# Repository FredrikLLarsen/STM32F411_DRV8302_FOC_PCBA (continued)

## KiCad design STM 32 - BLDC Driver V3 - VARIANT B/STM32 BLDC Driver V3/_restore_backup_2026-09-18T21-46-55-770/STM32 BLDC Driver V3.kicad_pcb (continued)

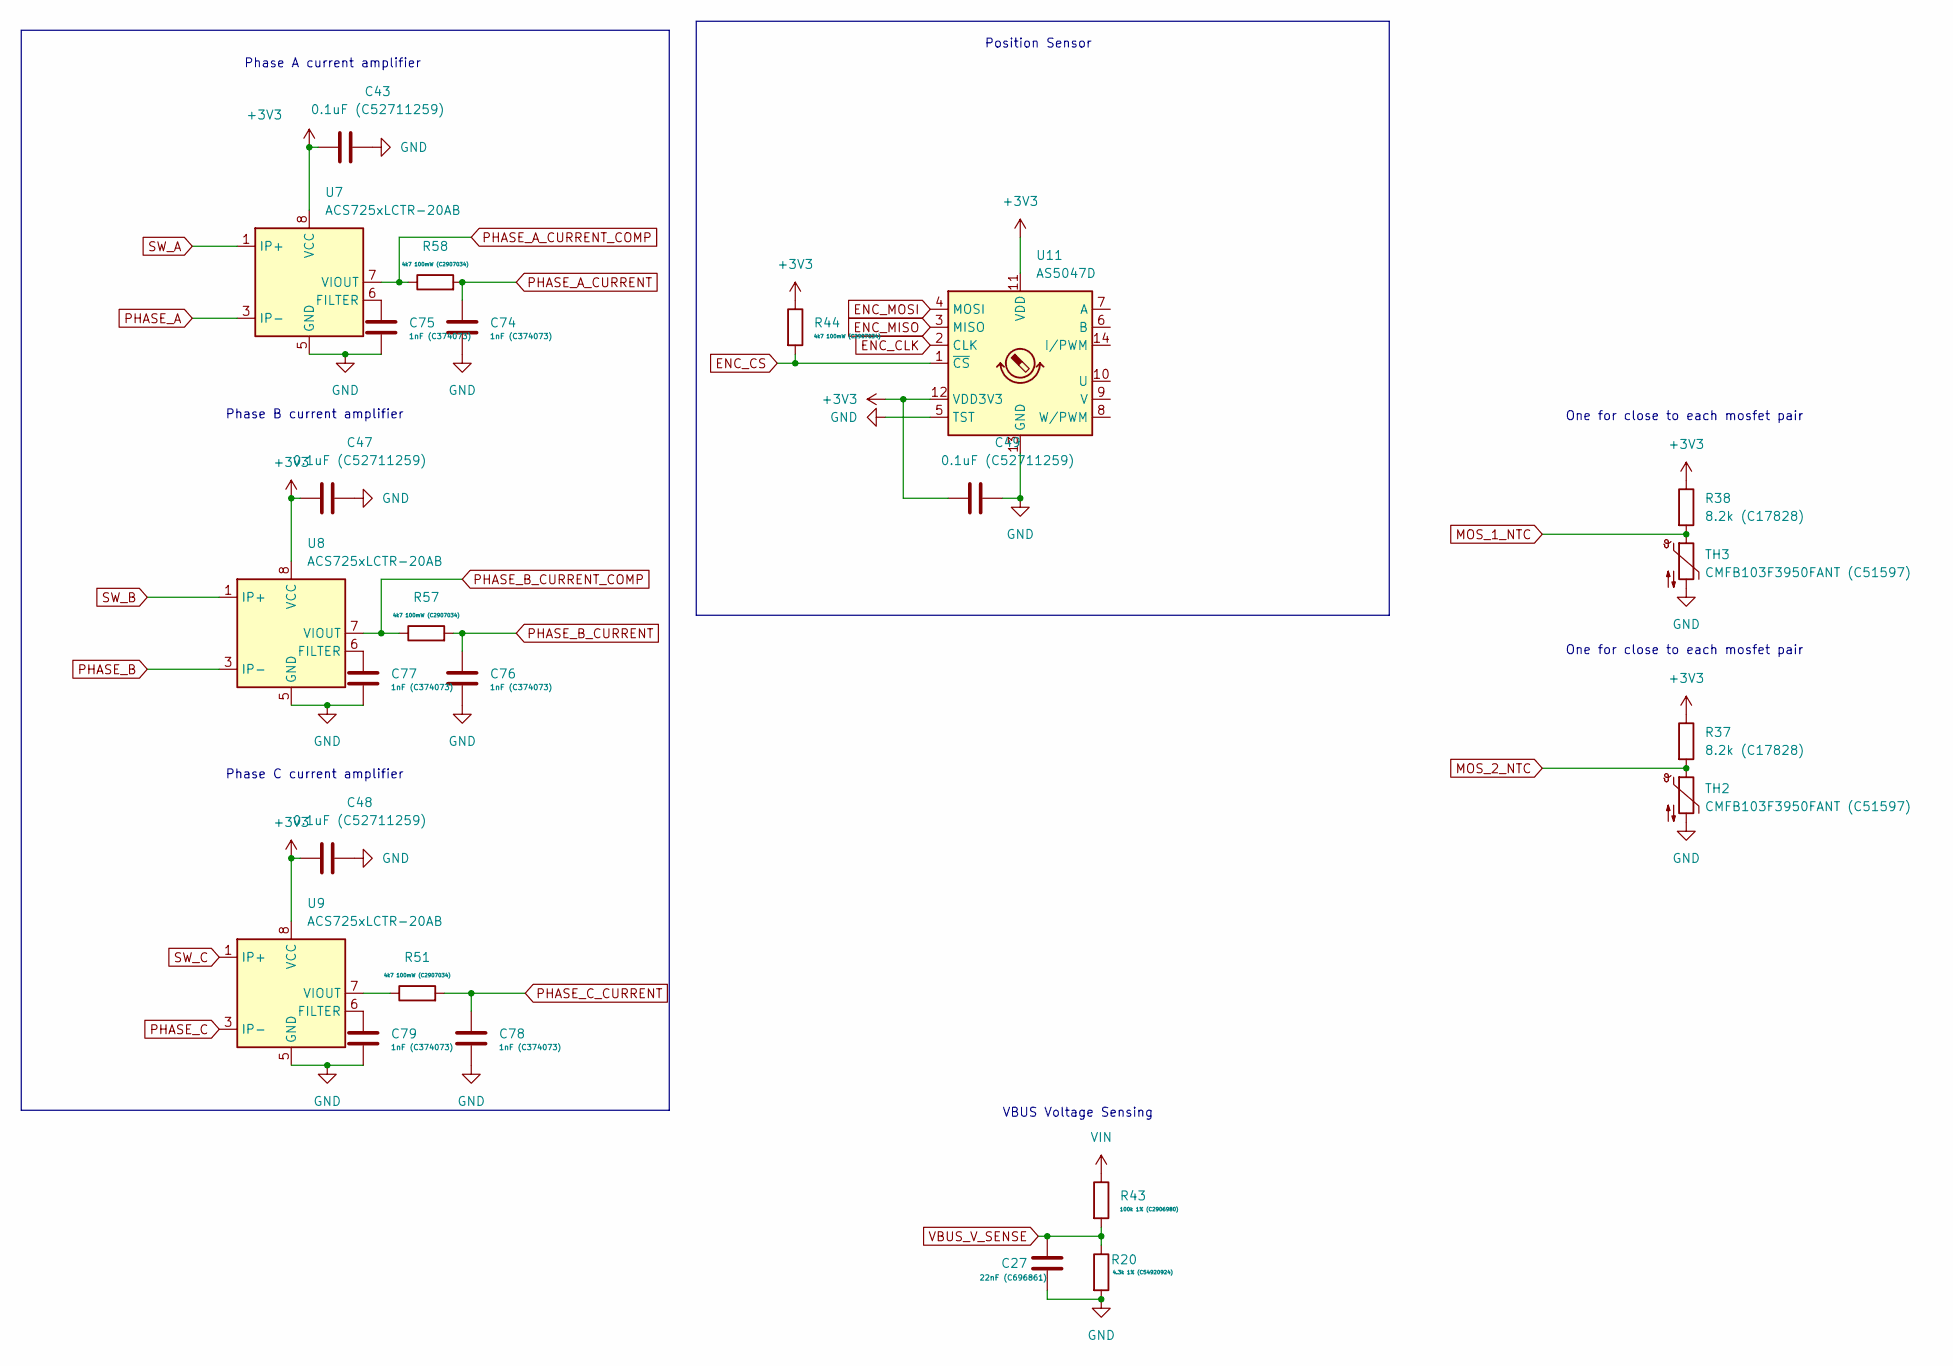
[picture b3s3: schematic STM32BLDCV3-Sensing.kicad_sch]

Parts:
C27: 22nF (C696861); C_0603_1608Metric_Pad1.08x0.95mm_HandSolder
C43, C47, C48, C49: 0.1uF (C52711259); C_0603_1608Metric_Pad1.08x0.95mm_HandSolder
C74, C75, C76, C77, C78, C79: 1nF (C374073); C_0603_1608Metric_Pad1.08x0.95mm_HandSolder
R20: 4.3k 1% (C54920924); R_0603_1608Metric_Pad0.98x0.95mm_HandSolder
R37, R38: 8.2k (C17828); R_0805_2012Metric_Pad1.20x1.40mm_HandSolder
R43: 100k 1% (C2906980); R_0603_1608Metric_Pad0.98x0.95mm_HandSolder
R44, R51, R57, R58: 4k7 100mW (C2907034); R_0603_1608Metric_Pad0.98x0.95mm_HandSolder
TH2, TH3: CMFB103F3950FANT (C51597); R_0805_2012Metric_Pad1.20x1.40mm_HandSolder
U7, U8, U9: ACS725xLCTR-20AB; SOIC-8_3.9x4.9mm_P1.27mm
U11: AS5047D; TSSOP-14_4.4x5mm_P0.65mm

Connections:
+3V3: C43.1, C47.1, C48.1, C49.1, R37.1, R38.1, R44.1, U7.8 (VCC), U8.8 (VCC), U9.8 (VCC), U11.11 (VDD), U11.12 (VDD3V3); also elsewhere on the board
ENC_CLK: U11.2 (CLK); also elsewhere on the board
ENC_CS: R44.2, U11.1 (~CS); also elsewhere on the board
ENC_MISO: U11.3 (MISO); also elsewhere on the board
ENC_MOSI: U11.4 (MOSI); also elsewhere on the board
GND: C27.2, C43.2, C47.2, C48.2, C49.2, C74.2, C75.2, C76.2, C77.2, C78.2, C79.2, R20.2, TH2.2, TH3.2, U7.5 (GND), U8.5 (GND), U9.5 (GND), U11.5 (TST), U11.13 (GND); also elsewhere on the board
MOS_1_NTC: R38.2, TH3.1; also elsewhere on the board
MOS_2_NTC: R37.2, TH2.1; also elsewhere on the board
unnamed: C75.1, U7.6 (FILTER)
unnamed: C77.1, U8.6 (FILTER)
unnamed: C79.1, U9.6 (FILTER)
unnamed: R51.1, U9.7 (VIOUT)
PHASE_A: U7.3 (IP-), U7.4 (IP-); also elsewhere on the board
PHASE_A_CURRENT: C74.1, R58.2; also elsewhere on the board
PHASE_A_CURRENT_COMP: R58.1, U7.7 (VIOUT); also elsewhere on the board
PHASE_B: U8.3 (IP-), U8.4 (IP-); also elsewhere on the board
PHASE_B_CURRENT: C76.1, R57.2; also elsewhere on the board
PHASE_B_CURRENT_COMP: R57.1, U8.7 (VIOUT); also elsewhere on the board
PHASE_C: U9.3 (IP-), U9.4 (IP-); also elsewhere on the board
PHASE_C_CURRENT: C78.1, R51.2; also elsewhere on the board
SW_A: U7.1 (IP+), U7.2 (IP+); also elsewhere on the board
SW_B: U8.1 (IP+), U8.2 (IP+); also elsewhere on the board
SW_C: U9.1 (IP+), U9.2 (IP+); also elsewhere on the board
VBUS_V_SENSE: C27.1, R20.1, R43.2; also elsewhere on the board
VIN: R43.1; also elsewhere on the board

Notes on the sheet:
Position Sensor
Phase A current amplifier
Phase B current amplifier
One for close to each mosfet pair
Phase C current amplifier
VBUS Voltage Sensing

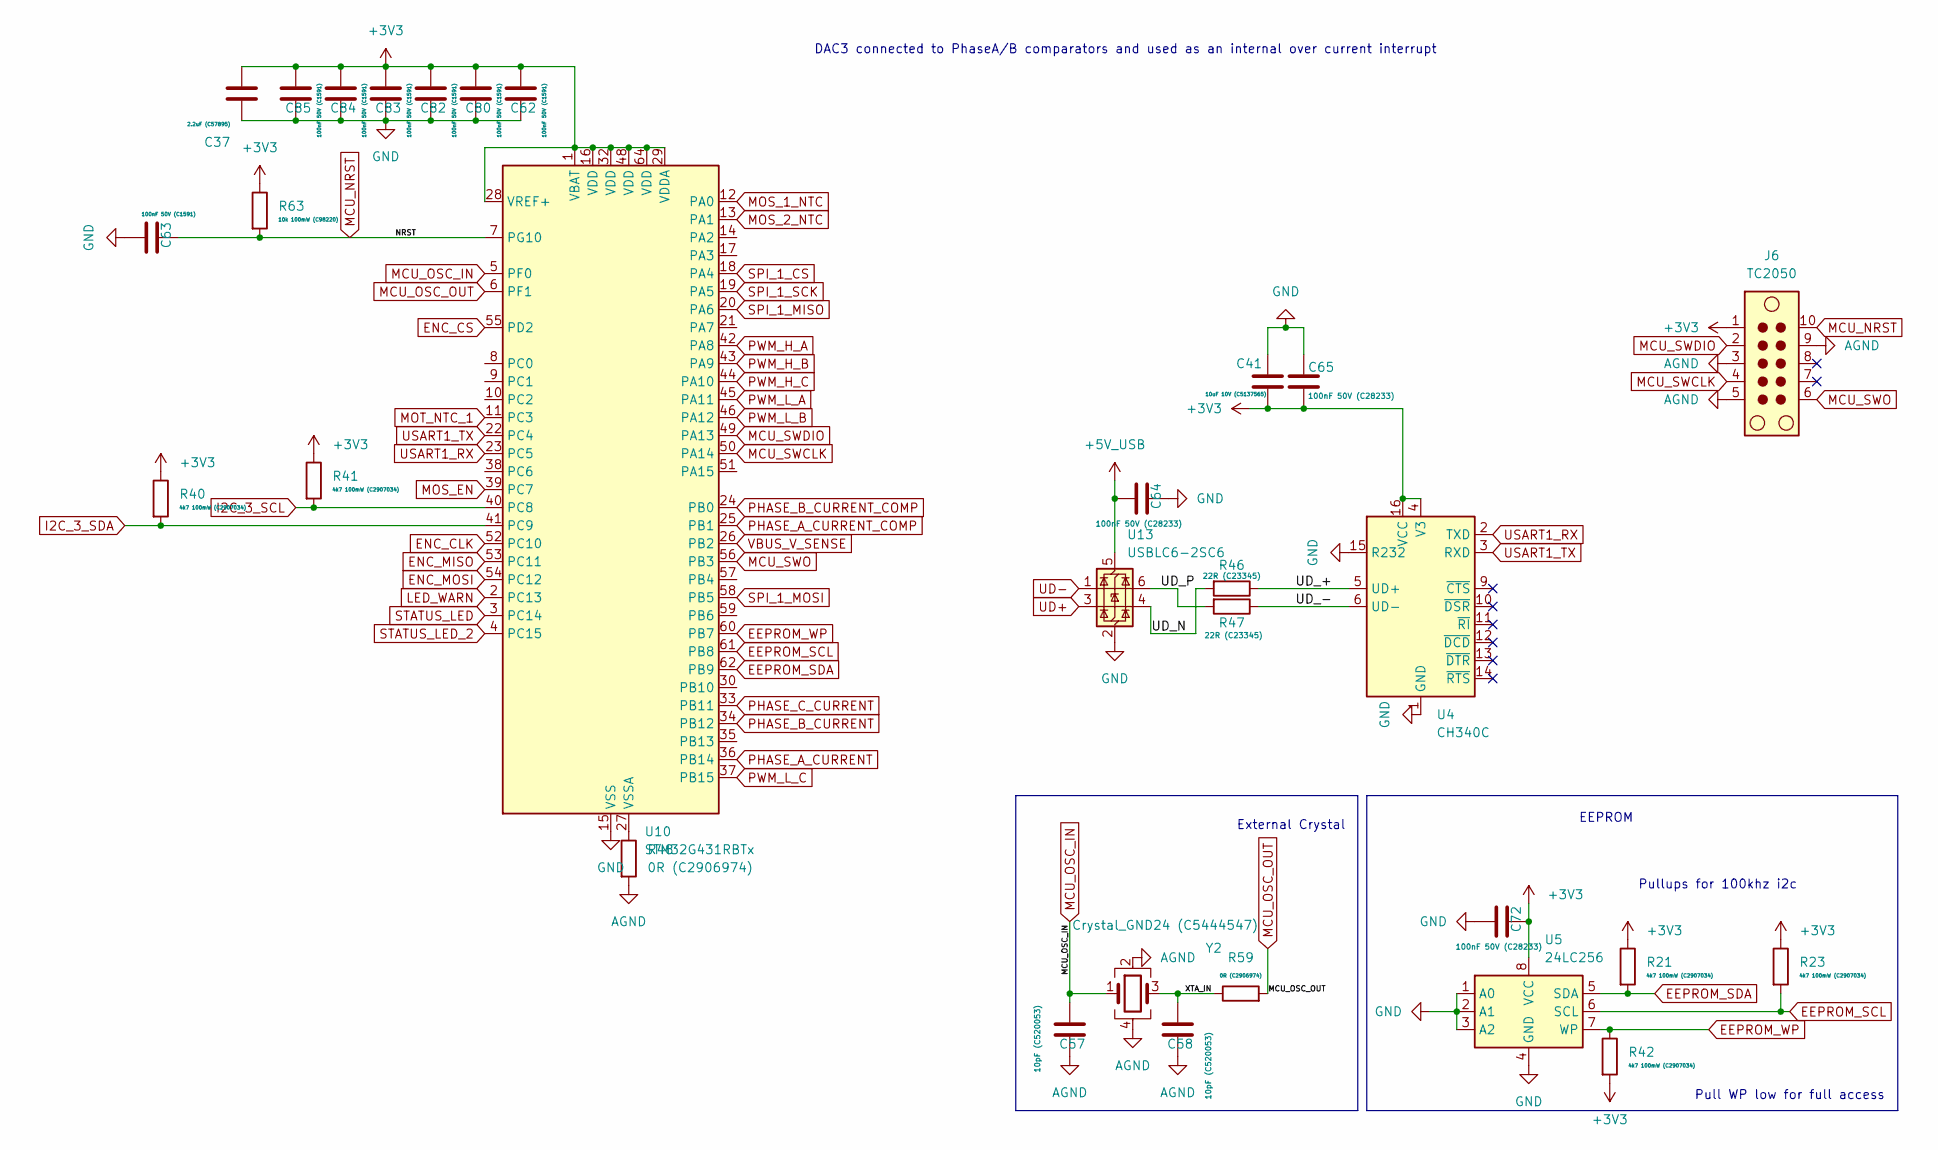
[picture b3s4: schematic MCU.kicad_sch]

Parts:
C37: 2.2uF (C57895); C_0603_1608Metric_Pad1.08x0.95mm_HandSolder
C41: 10uF 10V (C5137565); C_0603_1608Metric_Pad1.08x0.95mm_HandSolder
C57, C58: 10pF (C520053); C_0805_2012Metric_Pad1.18x1.45mm_HandSolder
C62, C63, C80, C82, C83, C84, C85: 100nF 50V (C1591); C_0603_1608Metric_Pad1.08x0.95mm_HandSolder
C64, C65, C72: 100nF 50V (C28233); C_0805_2012Metric_Pad1.18x1.45mm_HandSolder
J6: TC2050; Tag-Connect_TC2050-IDC-NL_2x05_P1.27mm_Vertical
R21, R23, R40, R41, R42: 4k7 100mW (C2907034); R_0603_1608Metric_Pad0.98x0.95mm_HandSolder
R46, R47: 22R (C23345); R_0603_1608Metric_Pad0.98x0.95mm_HandSolder
R48, R59: 0R (C2906974); R_0603_1608Metric_Pad0.98x0.95mm_HandSolder
R63: 10k 100mW (C98220); R_0603_1608Metric_Pad0.98x0.95mm_HandSolder
U4: CH340C; SOIC-16_3.9x9.9mm_P1.27mm
U5: 24LC256; SOIC-8_3.9x4.9mm_P1.27mm
U10: STM32G431RBTx; LQFP-64_10x10mm_P0.5mm
U13: USBLC6-2SC6; SOT-23-6
Y2: Crystal_GND24 (C5444547); Crystal_SMD_3225-4Pin_3.2x2.5mm_HandSoldering

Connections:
+3V3: C37.2, C41.1, C62.2, C65.2, C72.1, C80.2, C82.2, C83.2, C84.2, C85.2, J6.1, R21.1, R23.1, R40.1, R41.1, R42.2, R63.1, U4.4 (V3), U4.16 (VCC), U5.8 (VCC), U10.1 (VBAT), U10.16 (VDD), U10.28 (VREF+), U10.29 (VDDA), U10.32 (VDD), U10.48 (VDD), U10.64 (VDD); also elsewhere on the board
+5V_USB: C64.2, U13.5 (VBUS); also elsewhere on the board
/MCU/UD_+: R46.1, U4.5 (UD+)
/MCU/UD_-: R47.1, U4.6 (UD-)
/MCU/UD_N: R46.2, U13.4 (I/O2)
/MCU/UD_P: R47.2, U13.6 (I/O1)
/MCU/XTA_IN: C58.2, R59.1, Y2.3
AGND: C57.1, C58.1, J6.3, J6.5, J6.9, R48.2, Y2.2, Y2.4; also elsewhere on the board
EEPROM_SCL: R23.2, U5.6 (SCL), U10.61 (PB8)
EEPROM_SDA: R21.2, U5.5 (SDA), U10.62 (PB9)
EEPROM_WP: R42.1, U5.7 (WP), U10.60 (PB7)
ENC_CLK: U10.52 (PC10); also elsewhere on the board
ENC_CS: U10.55 (PD2); also elsewhere on the board
ENC_MISO: U10.53 (PC11); also elsewhere on the board
ENC_MOSI: U10.54 (PC12); also elsewhere on the board
GND: C37.1, C41.2, C62.1, C63.2, C64.1, C65.1, C72.2, C80.1, C82.1, C83.1, C84.1, C85.1, U4.1 (GND), U4.15 (R232), U5.1 (A0), U5.2 (A1), U5.3 (A2), U5.4 (GND), U10.15 (VSS), U10.31 (VSS), U10.47 (VSS), U10.63 (VSS), U13.2 (GND); also elsewhere on the board
I2C_3_SCL: R41.2, U10.40 (PC8); also elsewhere on the board
I2C_3_SDA: R40.2, U10.41 (PC9); also elsewhere on the board
LED_WARN: U10.2 (PC13); also elsewhere on the board
MCU_NRST: C63.1, J6.10, R63.2, U10.7 (PG10)
MCU_OSC_IN: C57.2, U10.5 (PF0), Y2.1
MCU_OSC_OUT: R59.2, U10.6 (PF1)
MCU_SWCLK: J6.4, U10.50 (PA14)
MCU_SWDIO: J6.2, U10.49 (PA13)
MCU_SWO: J6.6, U10.56 (PB3)
MOS_1_NTC: U10.12 (PA0); also elsewhere on the board
MOS_2_NTC: U10.13 (PA1); also elsewhere on the board
MOS_EN: U10.39 (PC7); also elsewhere on the board
MOT_NTC_1: U10.11 (PC3)
unnamed: R48.1, U10.27 (VSSA)
PHASE_A_CURRENT: U10.36 (PB14); also elsewhere on the board
PHASE_A_CURRENT_COMP: U10.25 (PB1); also elsewhere on the board
PHASE_B_CURRENT: U10.34 (PB12); also elsewhere on the board
PHASE_B_CURRENT_COMP: U10.24 (PB0); also elsewhere on the board
PHASE_C_CURRENT: U10.33 (PB11); also elsewhere on the board
PWM_H_A: U10.42 (PA8); also elsewhere on the board
PWM_H_B: U10.43 (PA9); also elsewhere on the board
PWM_H_C: U10.44 (PA10); also elsewhere on the board
PWM_L_A: U10.45 (PA11); also elsewhere on the board
PWM_L_B: U10.46 (PA12); also elsewhere on the board
PWM_L_C: U10.37 (PB15); also elsewhere on the board
SPI_1_CS: U10.18 (PA4); also elsewhere on the board
SPI_1_MISO: U10.20 (PA6); also elsewhere on the board
SPI_1_MOSI: U10.58 (PB5); also elsewhere on the board
SPI_1_SCK: U10.19 (PA5); also elsewhere on the board
STATUS_LED: U10.3 (PC14); also elsewhere on the board
STATUS_LED_2: U10.4 (PC15); also elsewhere on the board
UD+: U13.3 (I/O2); also elsewhere on the board
UD-: U13.1 (I/O1); also elsewhere on the board
USART1_RX: U4.2 (TXD), U10.23 (PC5)
USART1_TX: U4.3 (RXD), U10.22 (PC4)
VBUS_V_SENSE: U10.26 (PB2); also elsewhere on the board

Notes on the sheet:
External Crystal
EEPROM
Pull WP low for full access
DAC3 connected to PhaseA/B comparators and used as an internal over current interrupt
Pullups for 100khz i2c

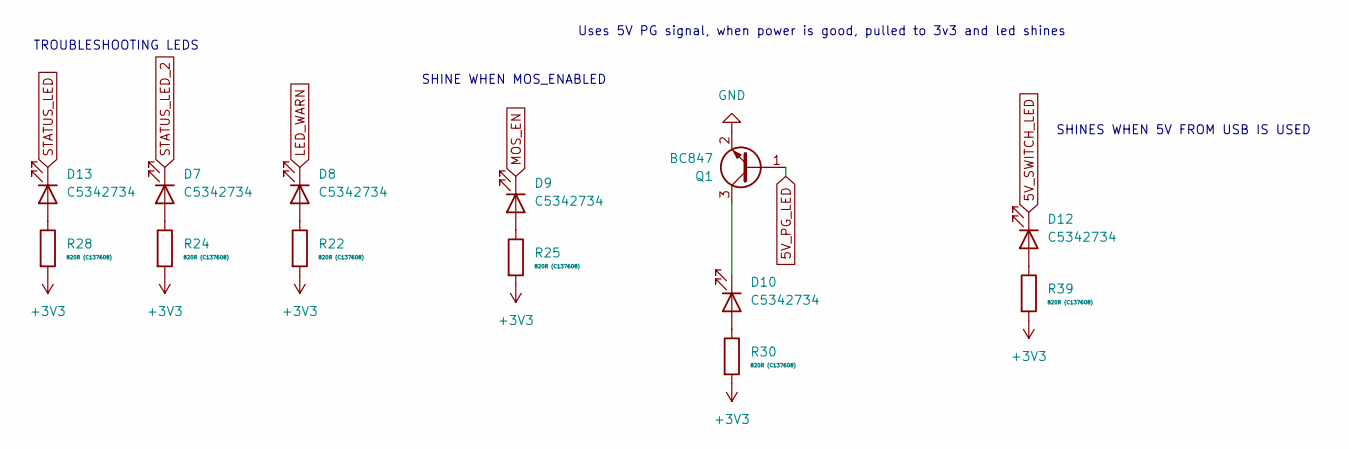
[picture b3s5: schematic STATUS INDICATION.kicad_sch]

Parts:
D7, D8, D9, D10, D12, D13: C5342734; LED_0603_1608Metric_Pad1.05x0.95mm_HandSolder
Q1: BC847; SOT-23
R22, R24, R25, R28, R30, R39: 820R (C137608); R_0603_1608Metric_Pad0.98x0.95mm_HandSolder

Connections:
5V_PG_LED: Q1.1 (B); also elsewhere on the board
5V_SWITCH_LED: D12.1 (K); also elsewhere on the board
+3V3: R22.2, R24.2, R25.2, R28.2, R30.2, R39.2; also elsewhere on the board
GND: Q1.2 (E); also elsewhere on the board
LED_WARN: D8.1 (K); also elsewhere on the board
MOS_EN: D9.1 (K); also elsewhere on the board
unnamed: D7.2 (A), R24.1
unnamed: D8.2 (A), R22.1
unnamed: D9.2 (A), R25.1
unnamed: D10.2 (A), R30.1
unnamed: D10.1 (K), Q1.3 (C)
unnamed: D12.2 (A), R39.1
unnamed: D13.2 (A), R28.1
STATUS_LED: D13.1 (K); also elsewhere on the board
STATUS_LED_2: D7.1 (K); also elsewhere on the board

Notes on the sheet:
TROUBLESHOOTING LEDS
Uses 5V PG signal, when power is good, pulled to 3v3 and led shines
SHINE WHEN MOS_ENABLED
SHINES WHEN 5V FROM USB IS USED

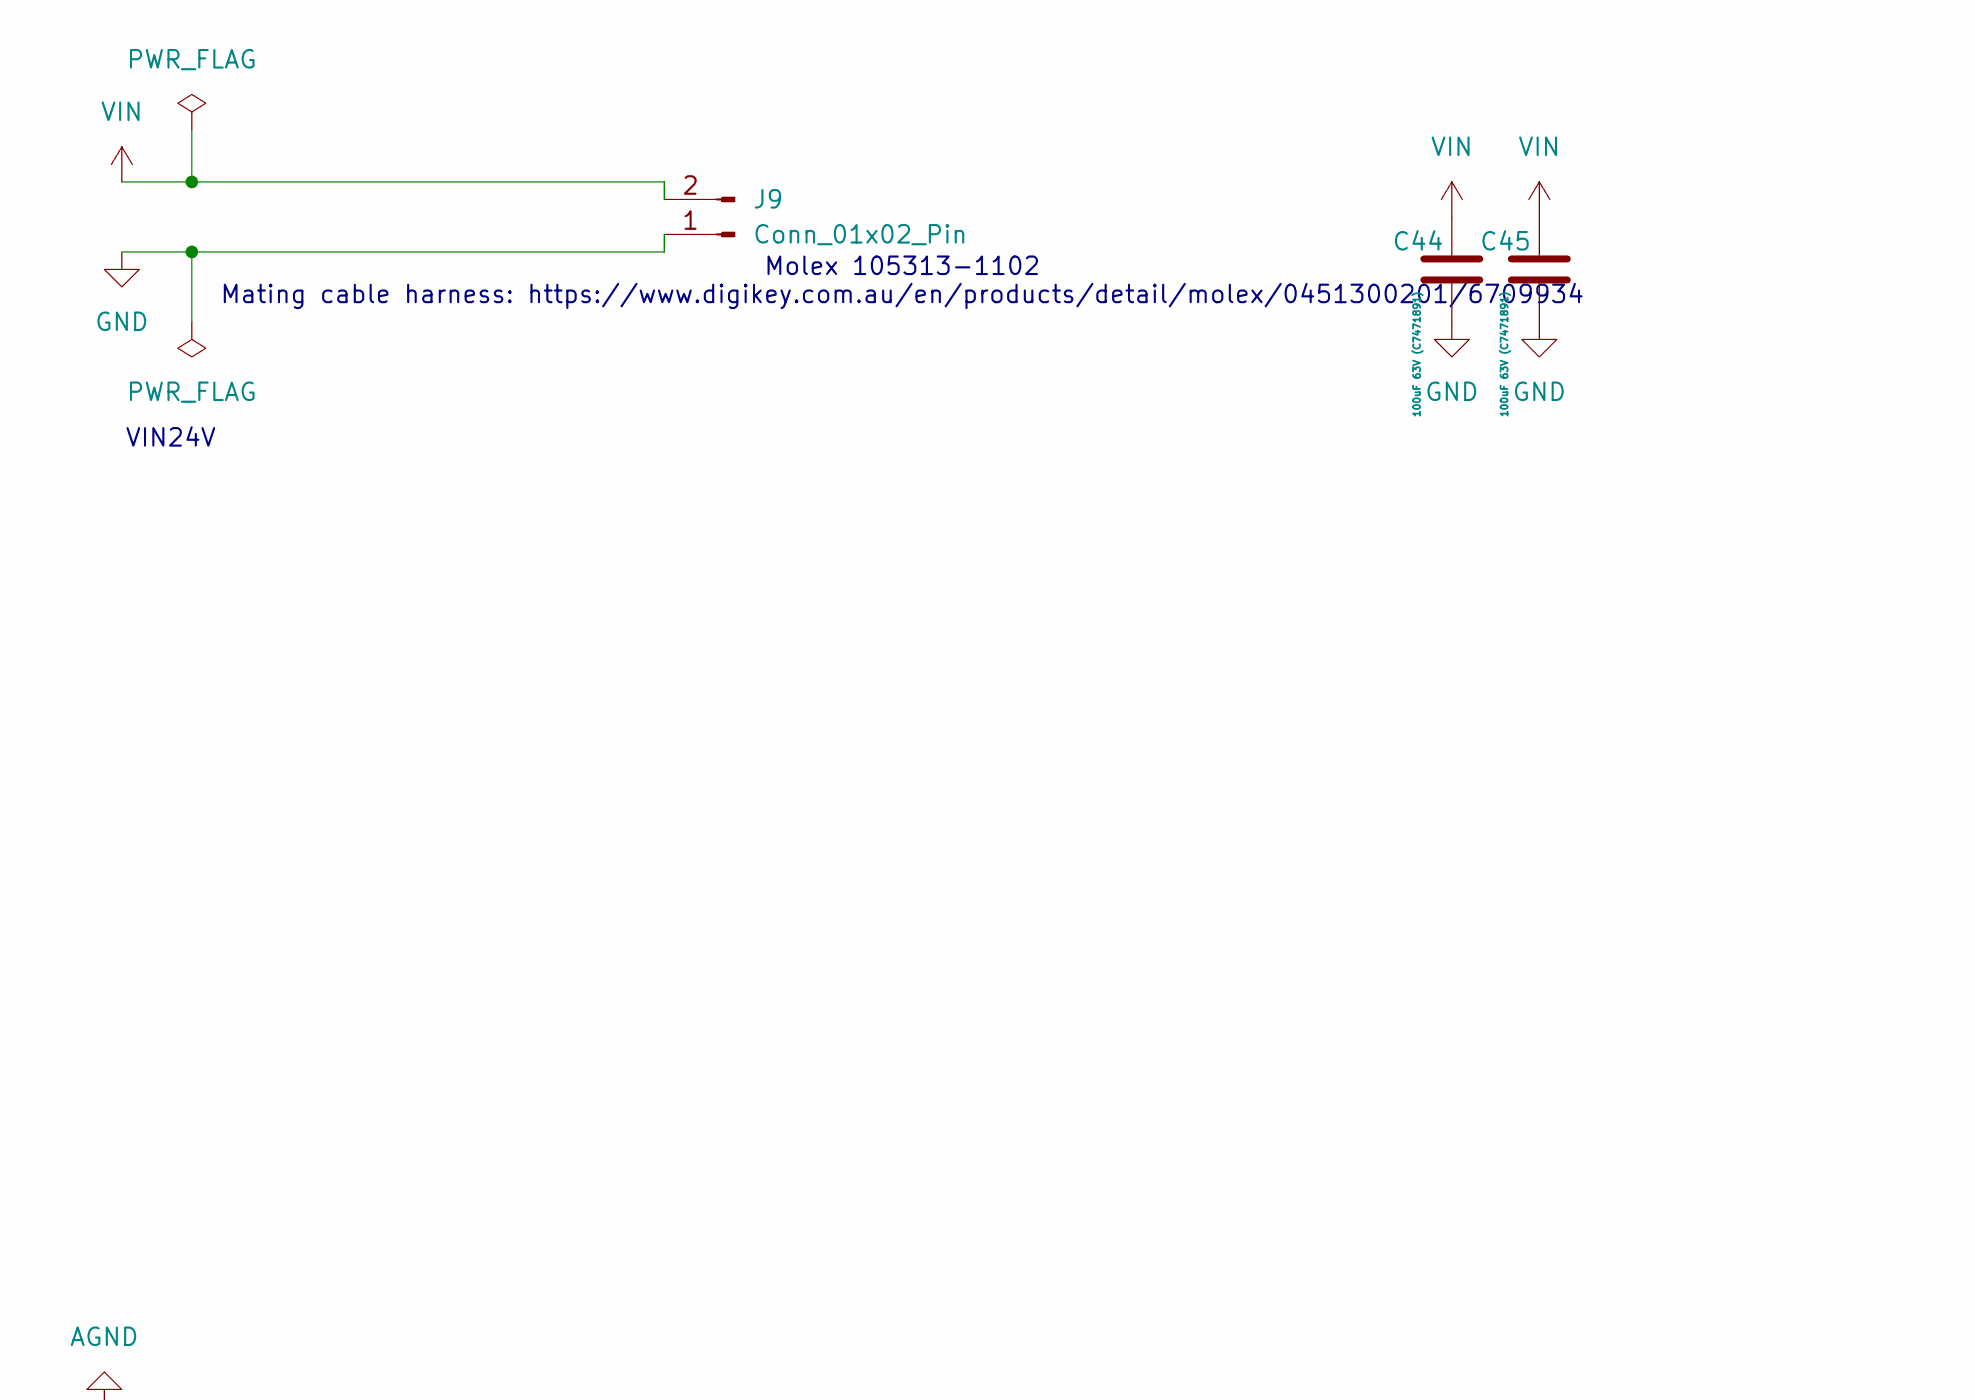
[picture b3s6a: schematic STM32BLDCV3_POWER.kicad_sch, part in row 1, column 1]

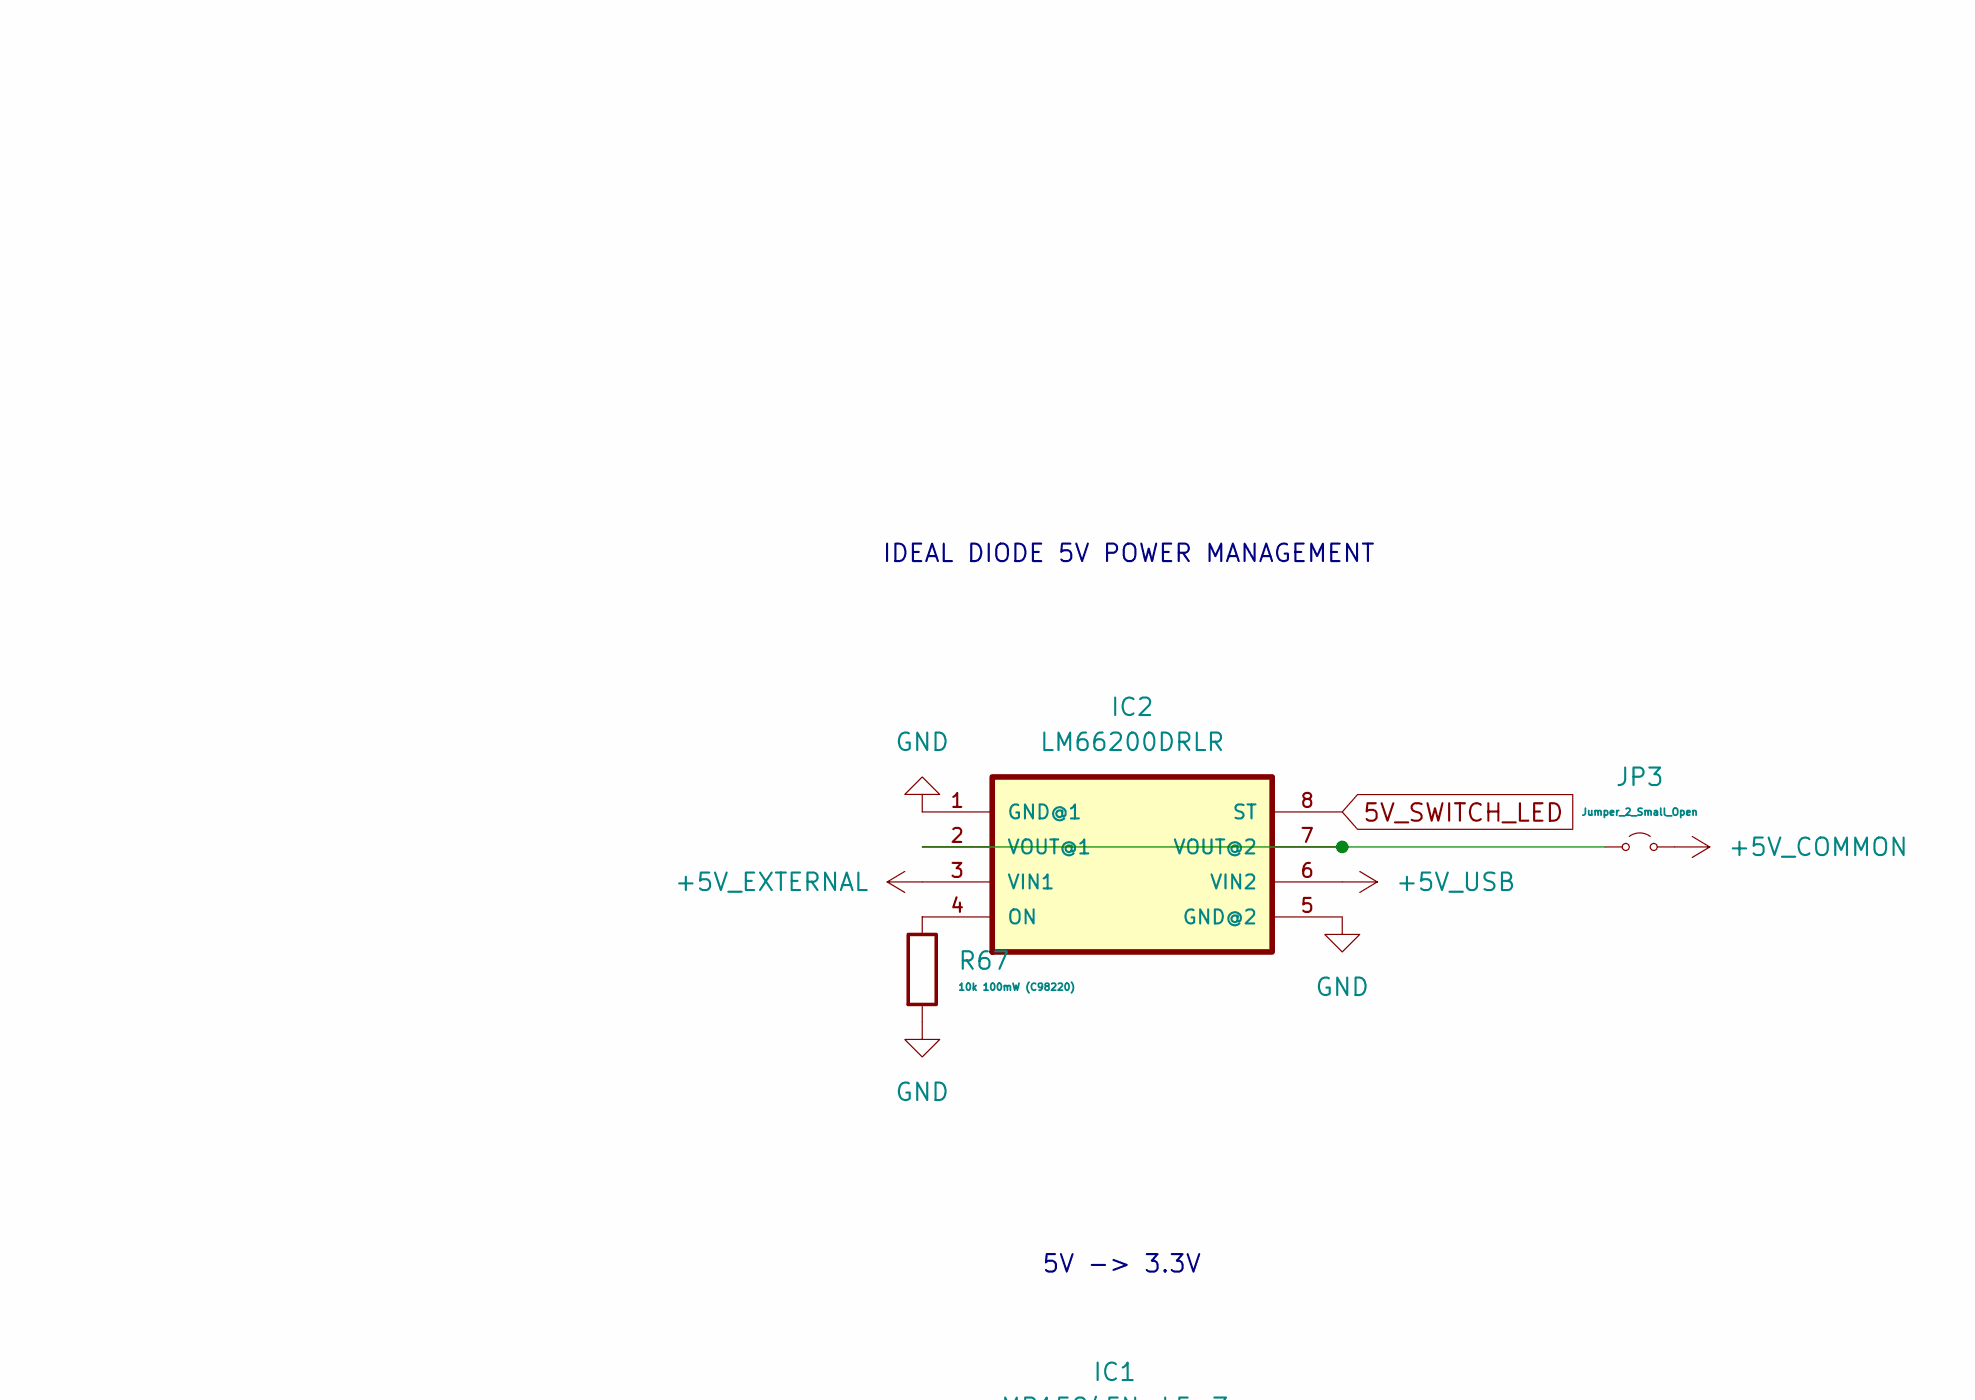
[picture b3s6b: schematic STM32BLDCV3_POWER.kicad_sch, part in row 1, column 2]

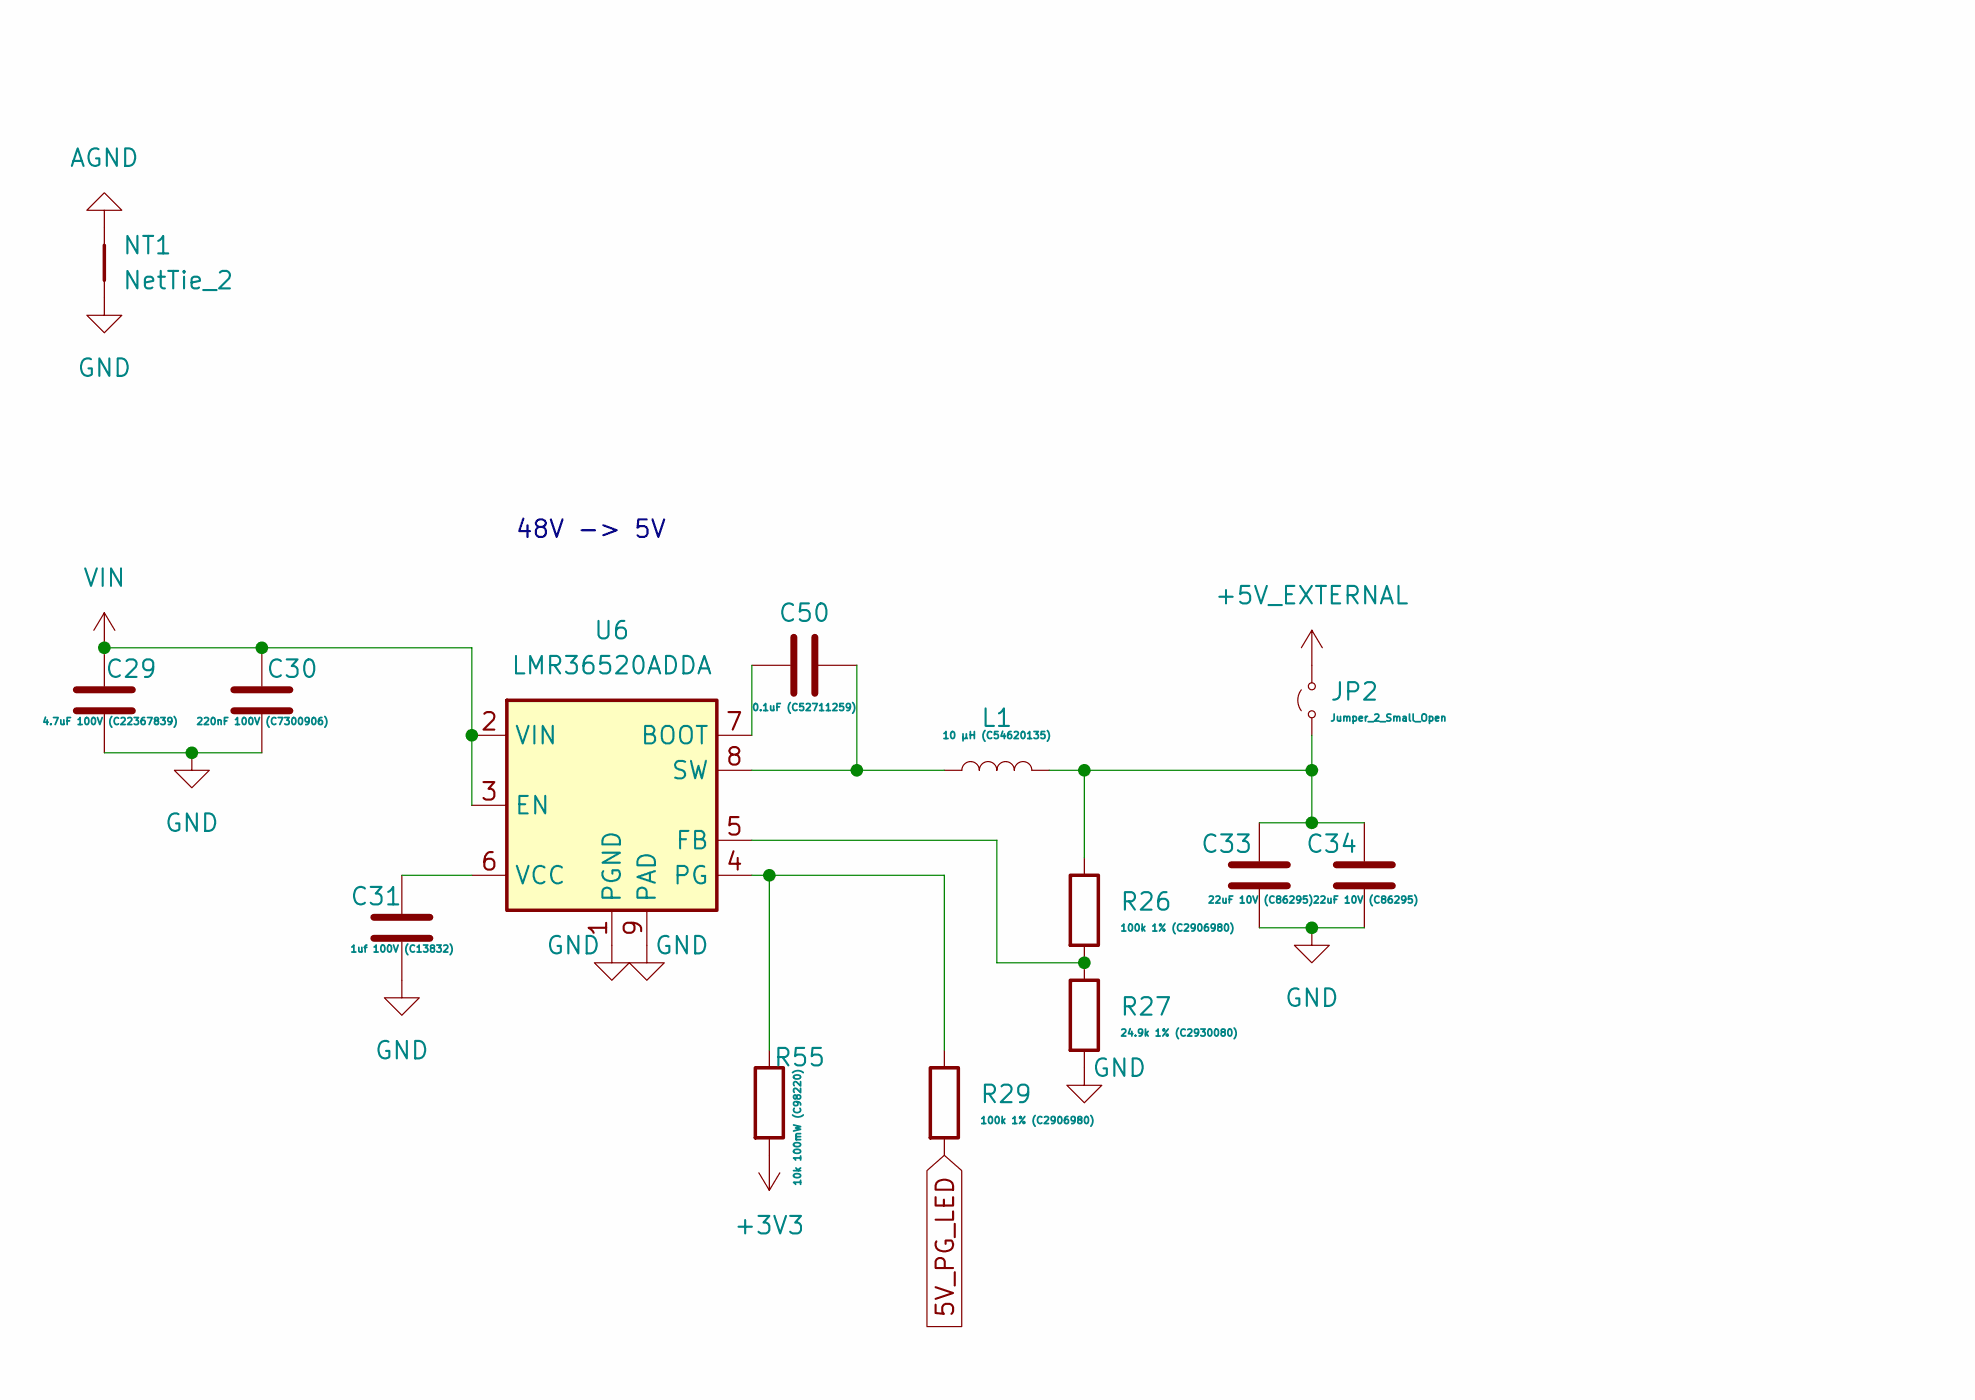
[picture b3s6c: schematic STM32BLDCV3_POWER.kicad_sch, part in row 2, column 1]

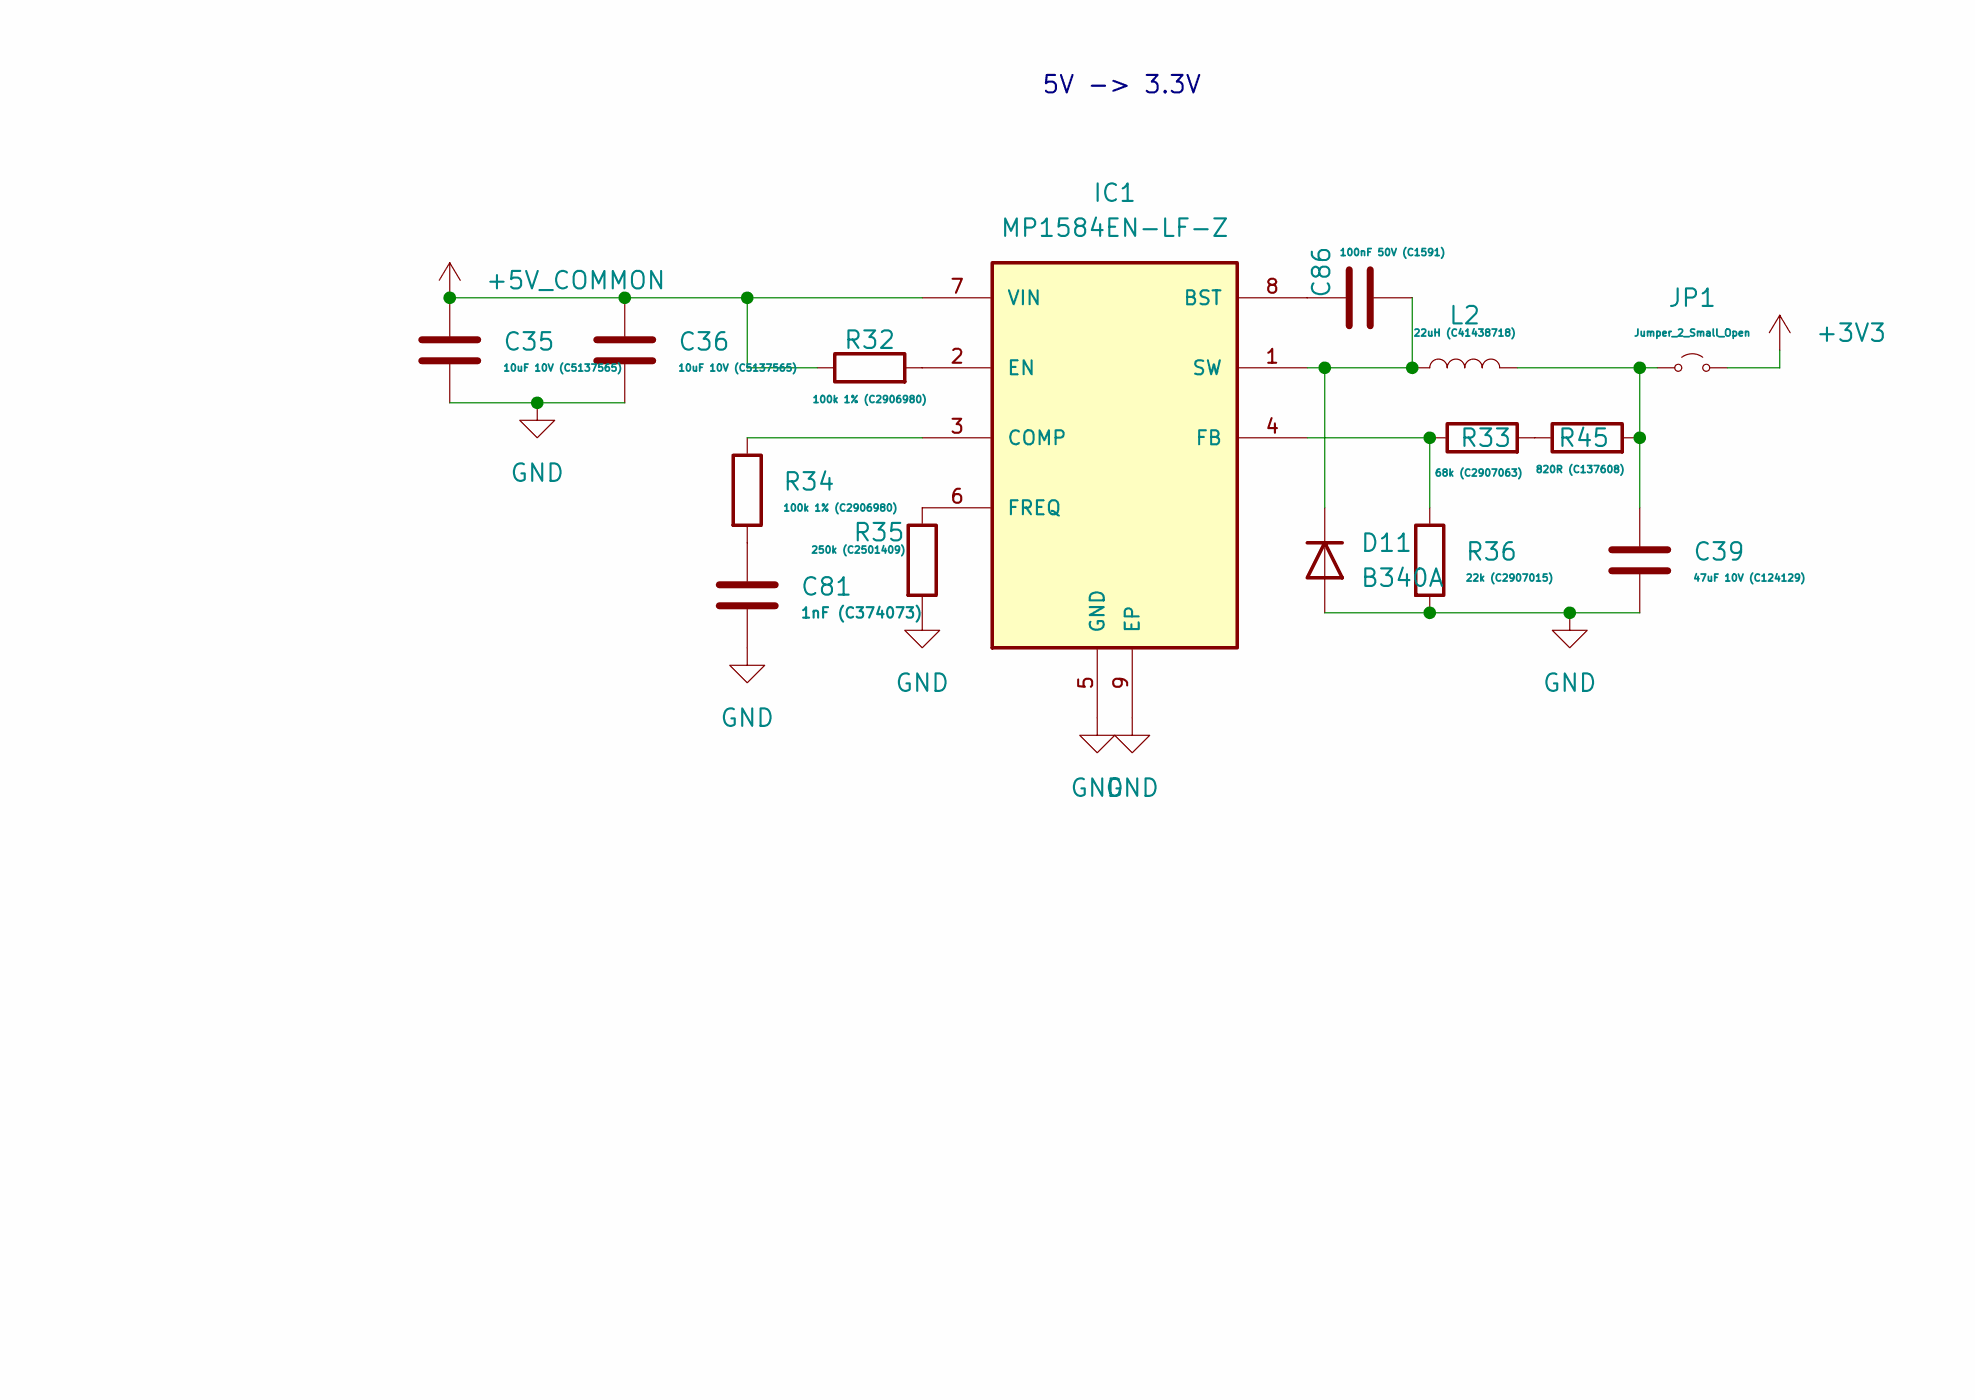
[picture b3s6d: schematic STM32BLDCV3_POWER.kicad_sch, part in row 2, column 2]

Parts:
C29: 4.7uF 100V (C22367839); C_1206_3216Metric_Pad1.33x1.80mm_HandSolder
C30: 220nF 100V (C7300906); C_0603_1608Metric_Pad1.08x0.95mm_HandSolder
C31: 1uf 100V (C13832); C_1206_3216Metric_Pad1.33x1.80mm_HandSolder
C33, C34: 22uF 10V (C86295); C_0603_1608Metric_Pad1.08x0.95mm_HandSolder
C35, C36: 10uF 10V (C5137565); C_0603_1608Metric_Pad1.08x0.95mm_HandSolder
C39: 47uF 10V (C124129); C_0805_2012Metric_Pad1.18x1.45mm_HandSolder
C44, C45: 100uF 63V (C7471891); C_Elec_8x10.2
C50: 0.1uF (C52711259); C_0603_1608Metric_Pad1.08x0.95mm_HandSolder
C81: 1nF (C374073); C_0603_1608Metric_Pad1.08x0.95mm_HandSolder
C86: 100nF 50V (C1591); C_0603_1608Metric_Pad1.08x0.95mm_HandSolder
D11: B340A; D_SMA_Handsoldering
IC1: MP1584EN-LF-Z; SOIC127P600X170-9N; MOUSER_PART_NUMBER 946-MP1584ENLFZ
IC2: LM66200DRLR; SOT8
J9: Conn_01x02_Pin; Molex_Nano-Fit_105313-xx02_1x02_P2.50mm_Horizontal
JP1, JP2, JP3: Jumper_2_Small_Open; SolderJumper-2_P1.3mm_Open_RoundedPad1.0x1.5mm
L1: 10 µH (C54620135); L_Abracon_ASPIAIG-F4020
L2: 22uH (C41438718); L_Sunlord_MWSA0402S
NT1: NetTie_2; NetTie-2_SMD_Pad0.5mm
R26, R29, R32, R34: 100k 1% (C2906980); R_0603_1608Metric_Pad0.98x0.95mm_HandSolder
R27: 24.9k 1% (C2930080); R_0603_1608Metric_Pad0.98x0.95mm_HandSolder
R33: 68k (C2907063); R_0603_1608Metric_Pad0.98x0.95mm_HandSolder
R35: 250k (C2501409); R_0805_2012Metric_Pad1.20x1.40mm_HandSolder
R36: 22k (C2907015); R_0603_1608Metric_Pad0.98x0.95mm_HandSolder
R45: 820R (C137608); R_0603_1608Metric_Pad0.98x0.95mm_HandSolder
R55, R67: 10k 100mW (C98220); R_0603_1608Metric_Pad0.98x0.95mm_HandSolder
U6: LMR36520ADDA; Texas_HTSOP-8-1EP_3.9x4.9mm_P1.27mm_EP2.95x4.9mm_Mask2.4x3.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

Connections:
5V_PG_LED: R29.2; also elsewhere on the board
5V_SWITCH_LED: IC2.8 (ST); also elsewhere on the board
+3V3: JP1.2 (B), R55.2; also elsewhere on the board
+5V_COMMON: C35.2, C36.2, IC1.7 (VIN), JP3.2 (B), R32.1; also elsewhere on the board
+5V_EXTERNAL: IC2.3 (VIN1), JP2.2 (B)
+5V_USB: IC2.6 (VIN2); also elsewhere on the board
AGND: NT1.2; also elsewhere on the board
GND: C29.2, C30.2, C31.2, C33.1, C34.1, C35.1, C36.1, C39.1, C44.1, C45.1, C81.2, D11.2 (A), IC1.5 (GND), IC1.9 (EP), IC2.1 (GND@1), IC2.5 (GND@2), J9.1, NT1.1, R27.2, R35.2, R36.2, R67.2, U6.1 (PGND), U6.9 (PAD); also elsewhere on the board
unnamed: C81.1, R34.2
unnamed: C86.1, D11.1 (K), IC1.1 (SW), L2.1
unnamed: C86.2, IC1.8 (BST)
unnamed: IC1.3 (COMP), R34.1
unnamed: IC1.2 (EN), R32.2
unnamed: IC1.4 (FB), R33.1, R36.1
unnamed: IC1.6 (FREQ), R35.1
unnamed: IC2.4 (ON), R67.1
unnamed: IC2.2 (VOUT@1), IC2.7 (VOUT@2), JP3.1 (A)
unnamed: C39.2, JP1.1 (A), L2.2, R45.2
unnamed: C33.2, C34.2, JP2.1 (A), L1.2, R26.1
unnamed: R33.2, R45.1
unnamed: C50.1, U6.7 (BOOT)
unnamed: R26.2, R27.1, U6.5 (FB)
unnamed: R29.1, R55.1, U6.4 (PG)
unnamed: C50.2, L1.1, U6.8 (SW)
unnamed: C31.1, U6.6 (VCC)
VIN: C29.1, C30.1, C44.2, C45.2, J9.2, U6.2 (VIN), U6.3 (EN); also elsewhere on the board

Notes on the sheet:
5V -> 3.3V
48V -> 5V
VIN24V
IDEAL DIODE 5V POWER MANAGEMENT
Molex 105313-1102 Mating cable harness: https://www.digikey.com.au/en/products/detail/molex/0451300201/6709934
